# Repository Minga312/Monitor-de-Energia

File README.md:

Um sistema completo para monitoramento de energia em tempo real, permitindo que você entenda seus gastos, identifique os aparelhos que mais consomem e tome decisões inteligentes para economizar na conta de luz.

Este projeto combina hardware customizado e um aplicativo mobile para oferecer uma solução de ponta a ponta. O coração do sistema é um ESP32 que lê dados de um sensor de corrente não-invasivo e os envia para um aplicativo, onde são traduzidos em informações claras e acionáveis sobre seu consumo e gastos em Reais (R$).

💡 Visão Geral do Projeto
Muitas vezes, a conta de luz chega como uma surpresa no fim do mês. O E-Mon foi criado para resolver esse problema, fornecendo um feedback instantâneo sobre seu consumo de energia.

Monitoramento em Tempo Real: Veja o consumo de energia da sua casa ou de um circuito específico em tempo real no seu celular.

Análise de Custos: O aplicativo converte o consumo em kWh para o custo real em Reais, com base na tarifa da sua concessionária de energia.

Hardware Aberto: O design da placa de circuito impresso (PCB) foi feito em KiCad e está totalmente disponível.

Firmware Robusto: Desenvolvido com ESP-IDF (framework nativo da Espressif) para máxima performance e controle do hardware.

⚙️  Arquitetura do Sistema
O sistema é dividido em três componentes principais:

Hardware (A Placa): Uma PCB customizada com um ESP32, um circuito de condicionamento de sinal para o sensor de corrente (SCT-013) e uma fonte de alimentação.

Firmware (A Inteligência Embarcada): O código que roda no ESP32, responsável por:

Ler os dados analógicos do sensor.

Calcular a corrente RMS, potência e energia consumida (kWh).

Disponibilizar os dados via Bluetooth ou Whatsapp.

Aplicativo Mobile (A Interface): Um app feito em MIT APP Inventor que:

Se conecta ao hardware via Bluetooth.

Exibe os dados de consumo em tempo real.

Permite ao usuário inserir o valor da tarifa (R$/kWh).

Calcula e exibe o custo acumulado em Reais.

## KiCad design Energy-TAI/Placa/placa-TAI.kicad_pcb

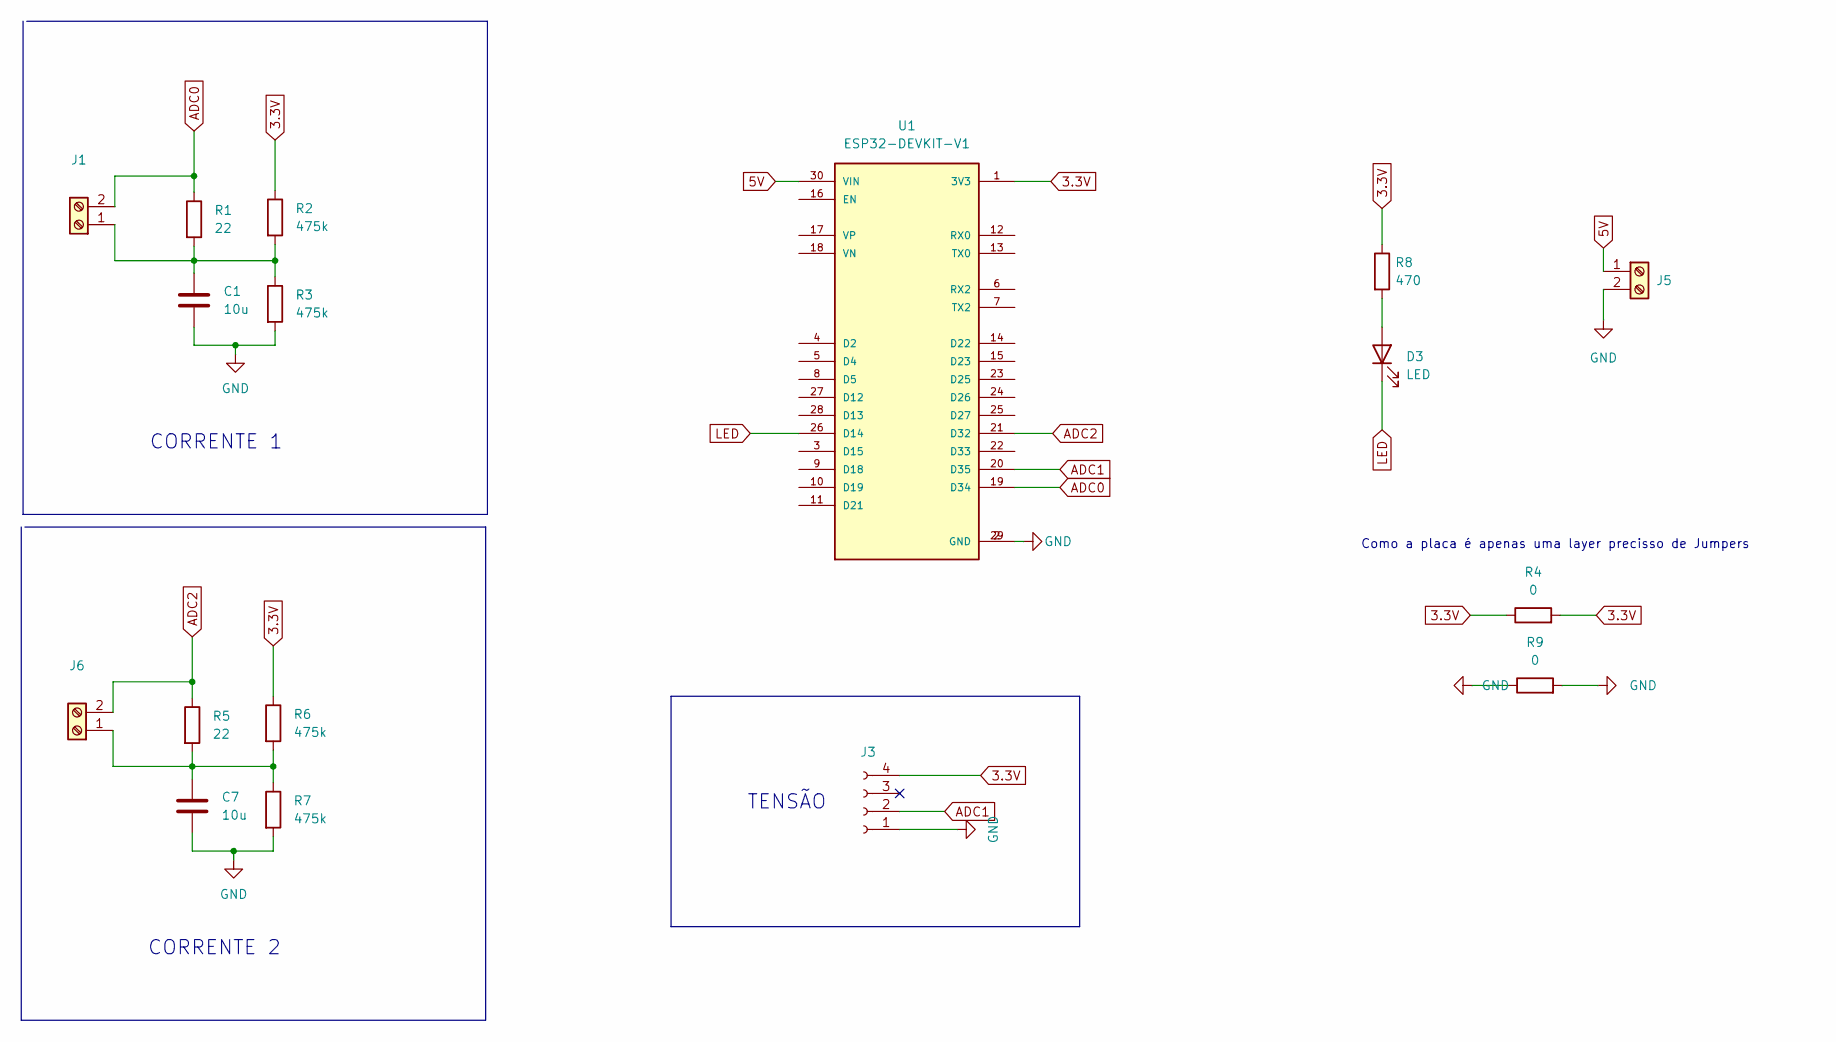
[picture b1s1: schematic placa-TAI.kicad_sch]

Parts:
C1, C7: 10u; C_Disc_D11.0mm_W5.0mm_P10.00mm
D3: LED; LED_D5.0mm_IRBlack
J1, J5, J6: Screw_Terminal_01x02; JWT_A3963_1x02_P3.96mm_Vertical
J3: Conn_01x04_Female; PinSocket_1x04_P2.54mm_Vertical
R1, R5: 22; R_Axial_DIN0207_L6.3mm_D2.5mm_P7.62mm_Horizontal
R2, R3, R6, R7: 475k; R_Axial_DIN0207_L6.3mm_D2.5mm_P7.62mm_Horizontal
R4, R9: 0; R_Axial_DIN0207_L6.3mm_D2.5mm_P7.62mm_Horizontal
R8: 470; R_Axial_DIN0207_L6.3mm_D2.5mm_P7.62mm_Horizontal
U1: ESP32-DEVKIT-V1; MODULE_ESP32_DEVKIT_V1; PARTREV N/A

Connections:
3.3V: J3.4, R2.1, R4.1, R4.2, R6.1, R8.1, U1.1 (3V3)
5V: J5.1, U1.30 (VIN)
ADC0: J1.2, R1.1, U1.19 (D34)
ADC1: J3.2, U1.20 (D35)
ADC2: J6.2, R5.1, U1.21 (D32)
GND: C1.2, C7.2, J3.1, J5.2, R3.2, R7.2, R9.1, R9.2, U1.2 (GND), U1.29 (GND)
LED: D3.1 (K), U1.26 (D14)
unnamed: C1.1, J1.1, R1.2, R2.2, R3.1
unnamed: C7.1, J6.1, R5.2, R6.2, R7.1
unnamed: D3.2 (A), R8.2

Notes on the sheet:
TENSÃO
CORRENTE 2
Como a placa é apenas uma layer precisso de Jumpers
CORRENTE 1

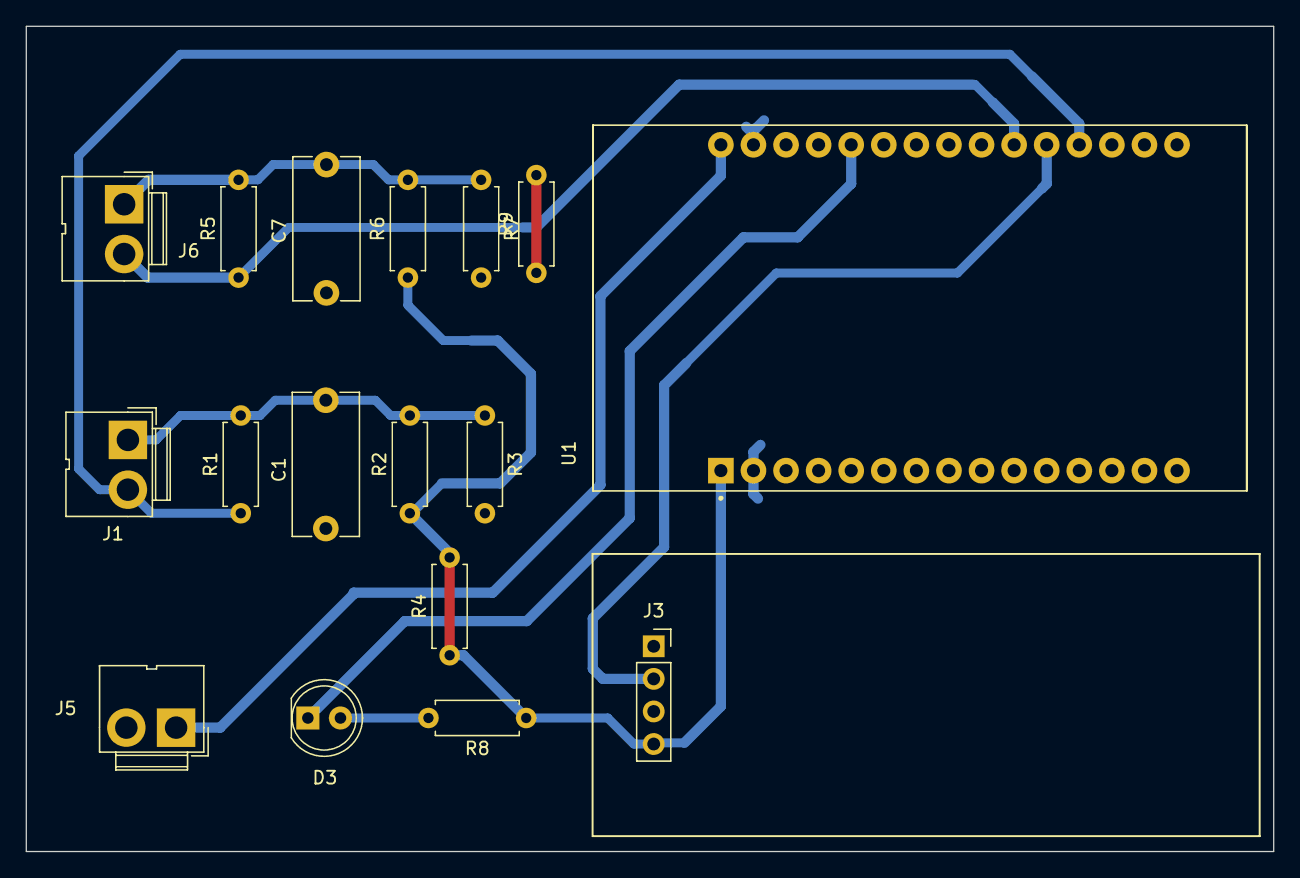
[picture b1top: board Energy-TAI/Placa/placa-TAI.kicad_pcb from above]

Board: 2 copper layers, 97.2 x 64.3 mm, 17 parts (0 on the bottom side), 10 nets.

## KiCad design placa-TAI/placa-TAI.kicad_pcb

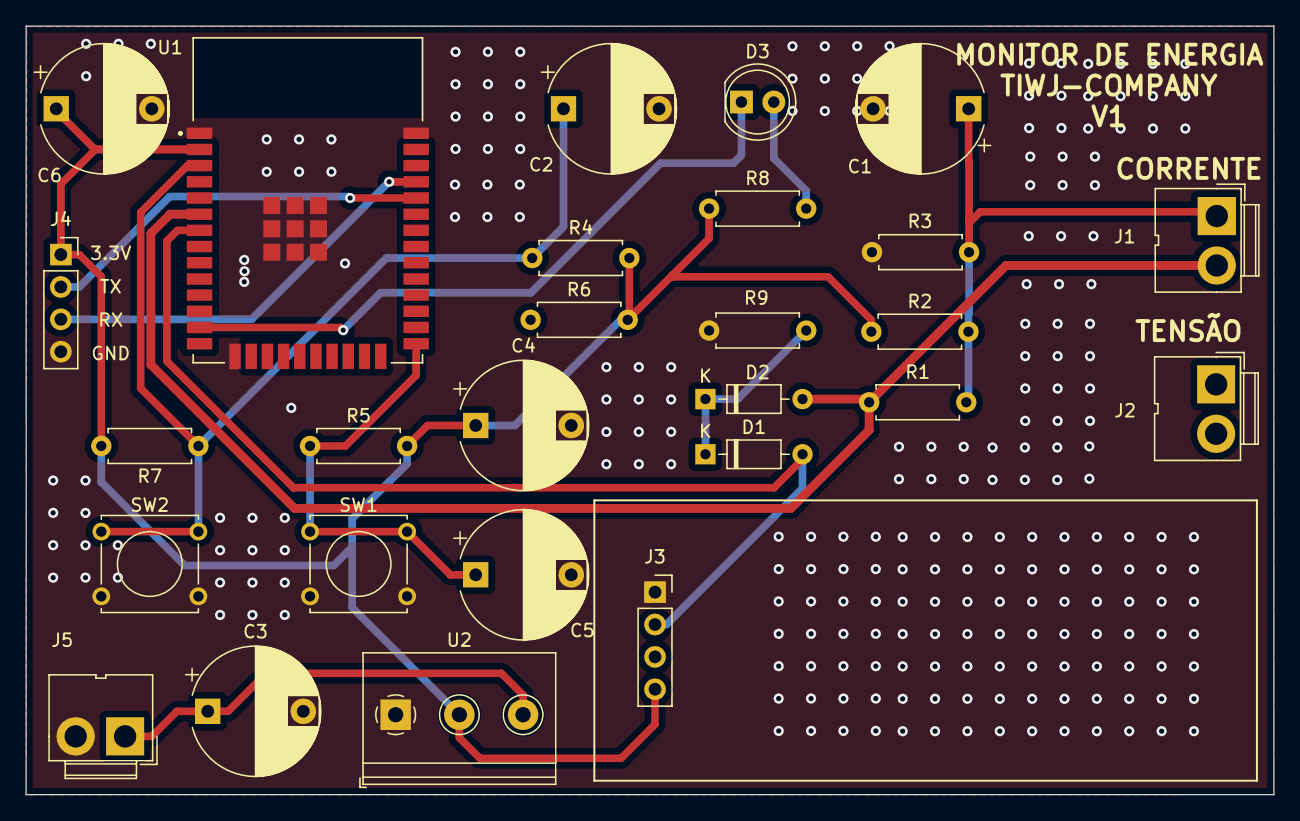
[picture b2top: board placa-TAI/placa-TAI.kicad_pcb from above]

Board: 2 copper layers, 97.9 x 60.3 mm, 27 parts (0 on the bottom side), 13 nets.

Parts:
C1: 10u; CP_Radial_D10.0mm_P7.50mm
C2, C5, C6: 100n; CP_Radial_D10.0mm_P7.50mm
C3, C4: 10uF; CP_Radial_D10.0mm_P7.50mm
D1, D2: DIODE; D_DO-35_SOD27_P7.62mm_Horizontal
D3: LED; LED_D5.0mm_IRBlack
J1, J2, J5: Screw_Terminal_01x02; JWT_A3963_1x02_P3.96mm_Vertical
J3: Conn_01x04_Female; PinSocket_1x04_P2.54mm_Vertical
J4: Conn_01x04_Male; PinSocket_1x04_P2.54mm_Vertical
R1: 22; R_Axial_DIN0207_L6.3mm_D2.5mm_P7.62mm_Horizontal
R2, R3: 475k; R_Axial_DIN0207_L6.3mm_D2.5mm_P7.62mm_Horizontal
R4, R5, R6, R7, R9: 10k; R_Axial_DIN0207_L6.3mm_D2.5mm_P7.62mm_Horizontal
R8: 470; R_Axial_DIN0207_L6.3mm_D2.5mm_P7.62mm_Horizontal
SW1, SW2: SW_Push; SW_Tactile_Straight_KSL0Axx1LFTR
U1: ESP32-WROOM-32; MODULE_ESP32-WROOM-32
U2: LM1117-3.3; TerminalBlock_Philmore_TB133_1x03_P5.00mm_Horizontal

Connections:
3.3V: C4.1, C6.1, J3.4, J4.1, R2.1, R4.2, R5.2, R6.2, R7.2, R8.1, U1.2 (3V3), U2.2 (VO)
5V: C3.1, J5.1, U2.3 (VI)
ADC0: D2.1 (A), J1.2, R1.1, U1.6 (IO34)
ADC1: D1.1 (A), J3.2, U1.7 (IO35)
ADCX: D1.2 (K), D2.2 (K), R9.1
FSH: C2.1, R4.1, R7.1, SW2.1, U1.3 (EN)
GND: C1.2, C2.2, C3.2, C4.2, C5.2, C6.2, J3.1, J4.4, J5.2, R3.2, R9.2, SW1.2, SW2.2, U1.1 (GND), U1.15 (GND), U1.38 (GND), U1.39_1 (GND), U1.39_2 (GND), U1.39_3 (GND), U1.39_4 (GND), U1.39_5 (GND), U1.39_6 (GND), U1.39_7 (GND), U1.39_8 (GND), U1.39_9 (GND), U2.1 (GND)
LED: D3.1 (K), U1.13 (IO14)
unnamed: C1.1, J1.1, R1.2, R2.2, R3.1
unnamed: D3.2 (A), R8.2
RST: C5.1, R5.1, SW1.1, U1.25 (IO0)
RX: J4.3, U1.35 (TXD0)
TX: J4.2, U1.34 (RXD0)

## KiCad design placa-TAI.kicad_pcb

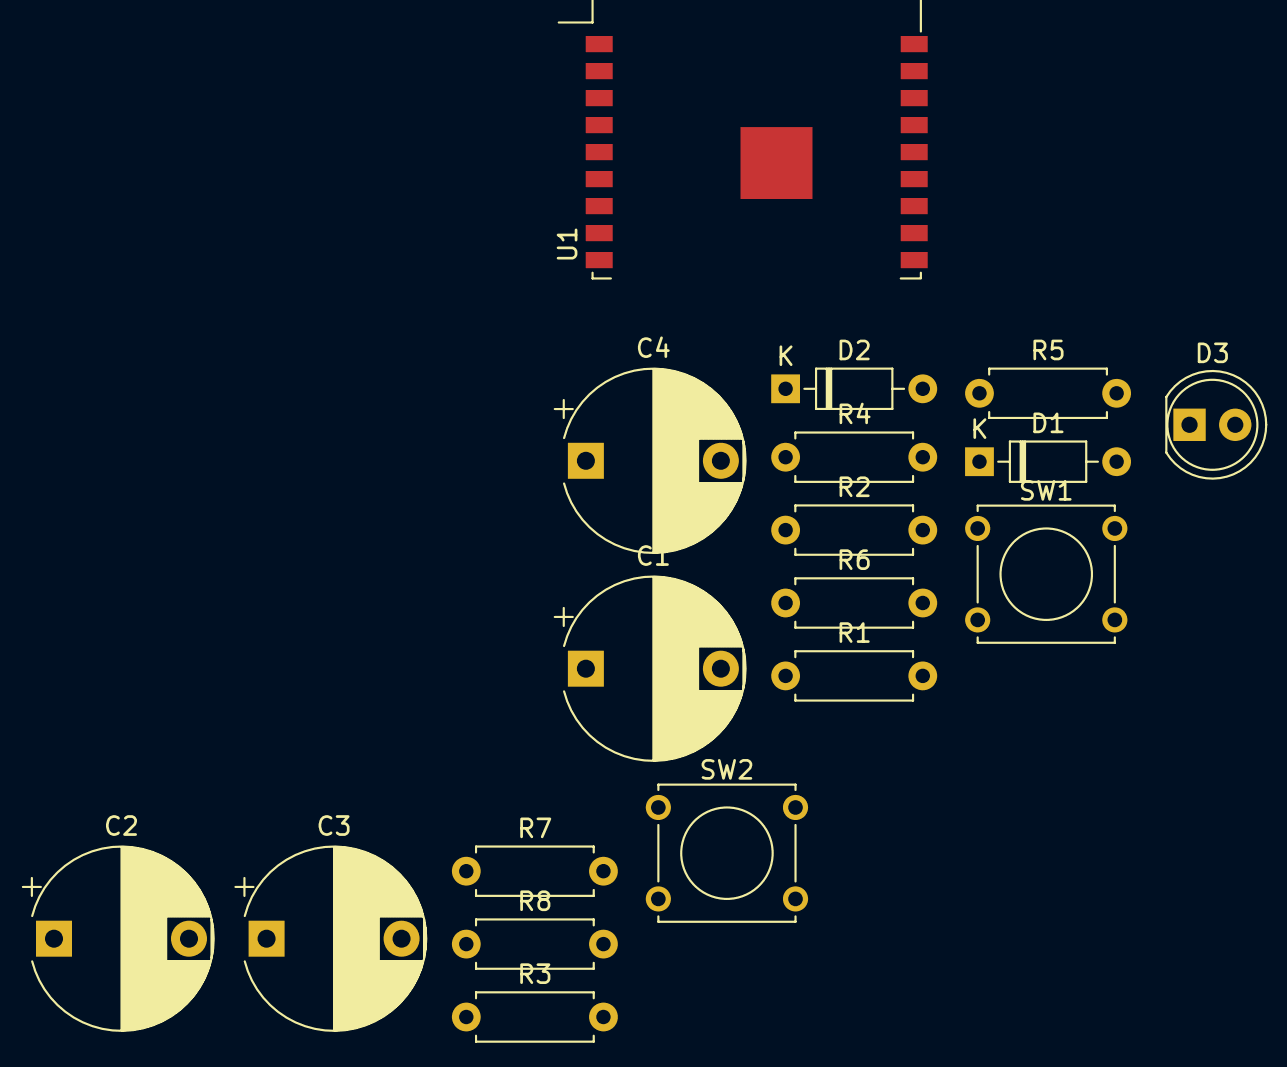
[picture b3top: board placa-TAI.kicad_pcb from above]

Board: 2 copper layers, 18 parts (0 on the bottom side), 12 nets, no tracks yet.

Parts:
C1: 10u; CP_Radial_D10.0mm_P7.50mm
C2: 100n; CP_Radial_D10.0mm_P7.50mm
C3, C4: 10uF; CP_Radial_D10.0mm_P7.50mm
D1, D2: DIODE; D_DO-35_SOD27_P7.62mm_Horizontal
D3: LED; LED_D5.0mm_IRBlack
R1: 22; R_Axial_DIN0207_L6.3mm_D2.5mm_P7.62mm_Horizontal
R2, R3, R8: 475k; R_Axial_DIN0207_L6.3mm_D2.5mm_P7.62mm_Horizontal
R4, R5, R6, R7: 10k; R_Axial_DIN0207_L6.3mm_D2.5mm_P7.62mm_Horizontal
SW1, SW2: SW_Push; SW_Tactile_Straight_KSL0Axx1LFTR
U1: ESP-WROOM-02

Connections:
3.3V: C2.1, C4.1, R4.2, R5.2, R6.2, R7.2, R8.1, U1.1 (VDD)
ADC0: D2.1 (A), R1.1
ADCX: D1.2 (K), D2.2 (K), U1.16 (TOUT)
CORRENTE_CONTROL: R2.1, U1.3 (IO14)
FSH: R7.1, SW2.1, U1.8 (IO0)
GND: C1.2, C2.2, C3.2, C4.2, R3.2, SW1.2, SW2.2, U1.9 (GND), U1.13 (GND), U1.18 (GND), U1.19 (GND)
LED: D3.1 (K), U1.6 (IO15)
unnamed: C1.1, R1.2, R2.2, R3.1
unnamed: D3.2 (A), R8.2
unnamed: R4.1, U1.2 (EN)
unnamed: R6.1, U1.10 (IO4)
RST: R5.1, SW1.1, U1.15 (RST), U1.17 (IO16)

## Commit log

2023-02-27 Inicio da placa
2023-02-27 Add files via upload
    Inicio do projeto
2023-03-01 Add files via upload
    Alterei o esp82 para o esp32
2023-03-20 Separando a placa do codigo
2023-03-21 Add files via upload
    Tive que alterar a placa para poder ser feita manualmente, pois houve taxação da nossa compra na china
2023-03-23 Codigo funcional para testar adc, aparentemente o problema e minha placa
2023-04-29 Lendo a tensao corretamente
2023-05-05 Lendo tensao e corrente corretamente
2023-05-09 Está compilando
2023-05-09 Wifi e bluetooth estao funcionando corretamente falta consertar a mensagem[
2023-05-09 Realmente o problema esta na mensg do wpp
2023-05-09 Consertei o problema da mensagem
2023-05-09 Colocado os ultimos envios para salvar
2023-05-09 Aguardando o aplicativo e teste real
2023-05-09 Colocando a função do wifi ligadda novamente
2023-05-09 Consertando o kwhr
2023-05-12 Colocando a leitura em outra core pois estava reiniciando
2023-09-21 Update README.md
    so salvando
2023-09-21 Create teste.py
    testeasd
2025-07-27 Update README.md
    Alterando README
2025-07-27 Update README.md
    Alterando visualização do readme
